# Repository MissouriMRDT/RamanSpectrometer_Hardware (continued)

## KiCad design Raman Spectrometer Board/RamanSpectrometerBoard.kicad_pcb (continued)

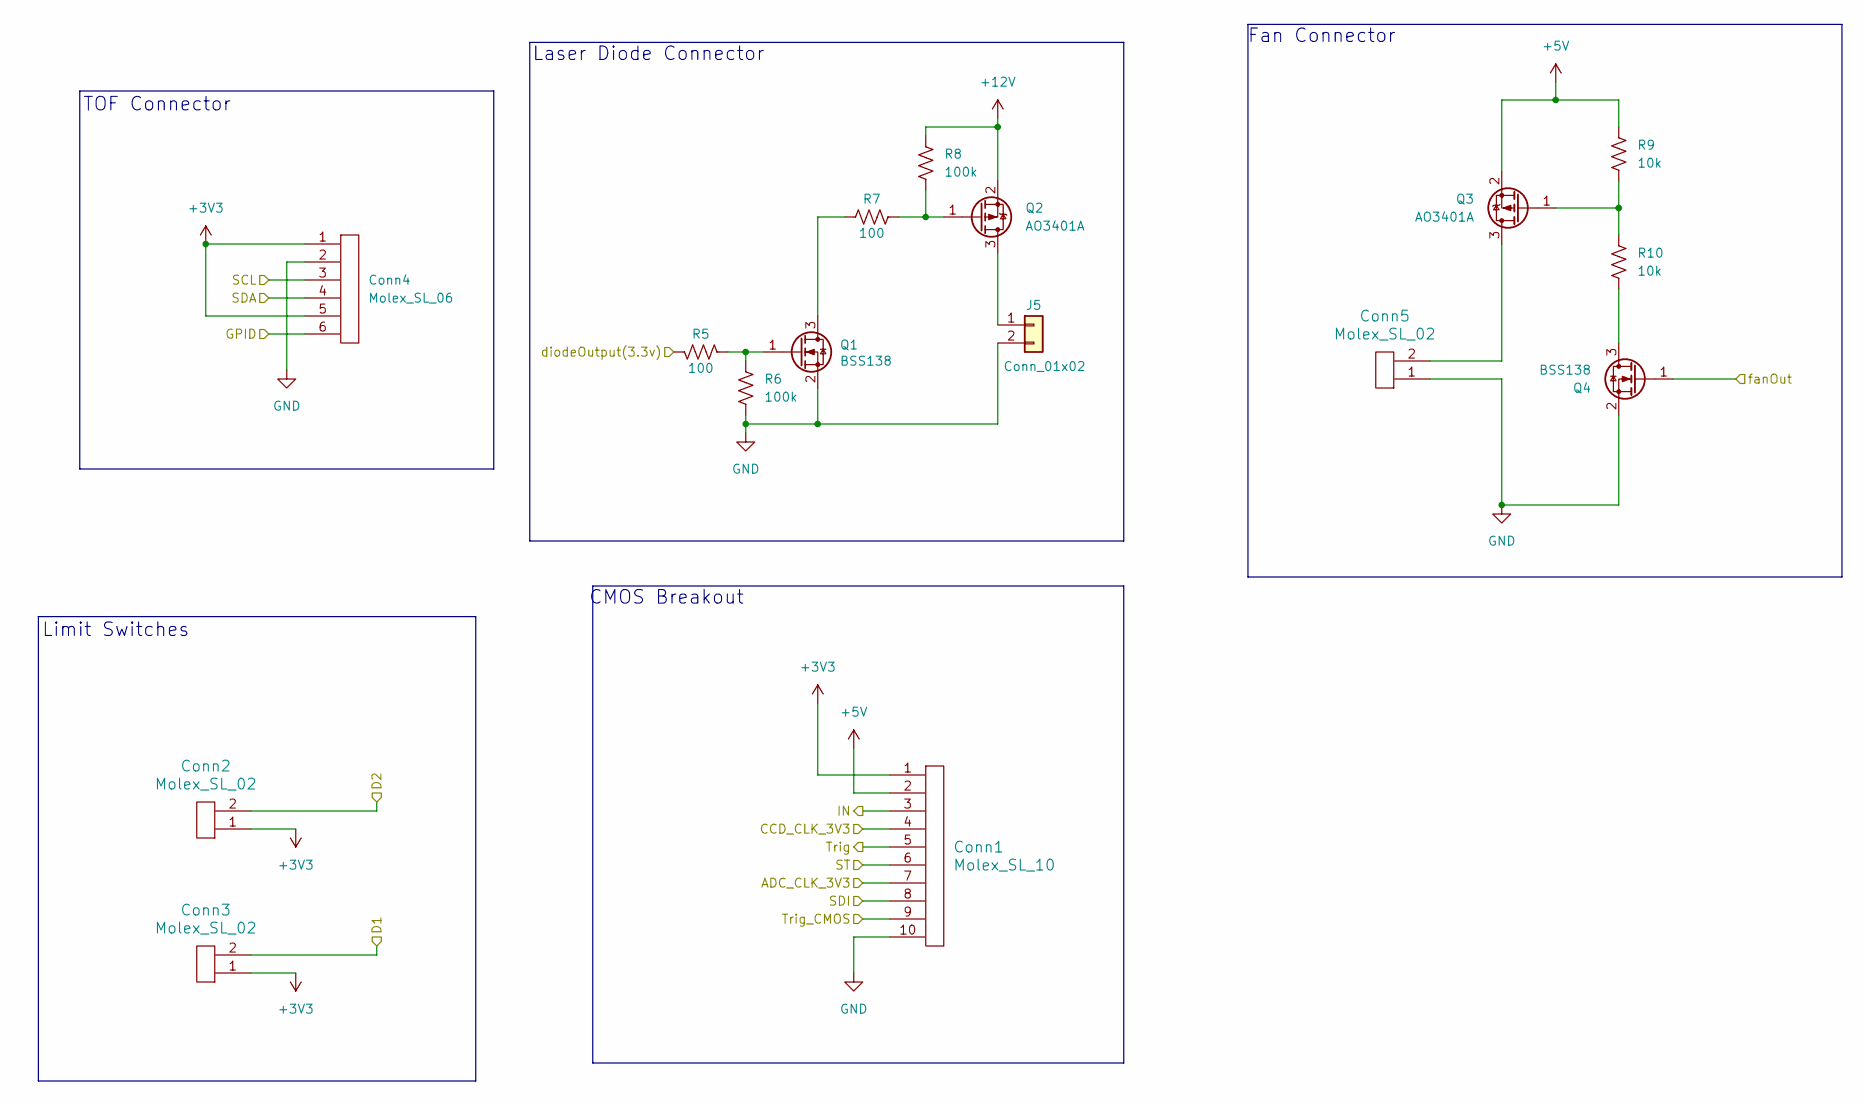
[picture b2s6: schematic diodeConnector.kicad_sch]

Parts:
Conn1: Molex_SL_10; MOLEX_SL_10_Vertical
Conn2, Conn3, Conn5: Molex_SL_02; MOLEX_SL_02_Vertical
Conn4: Molex_SL_06; MOLEX_SL_06_Vertical
J5: Conn_01x02; JST_EH_S2B-EH_1x02_P2.50mm_Horizontal
Q1, Q4: BSS138; SOT-23
Q2, Q3: AO3401A; SOT-23
R5, R7: 100; R_0603_1608Metric_Pad0.98x0.95mm_HandSolder
R6, R8: 100k; R_0603_1608Metric_Pad0.98x0.95mm_HandSolder
R9, R10: 10k; R_0603_1608Metric_Pad0.98x0.95mm_HandSolder

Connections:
+3V3: Conn1.1, Conn2.1, Conn3.1, Conn4.1, Conn4.5; also elsewhere on the board
+5V: Conn1.2, Q3.2 (S), R9.1; also elsewhere on the board
+12V: Q2.2 (S), R8.2; also elsewhere on the board
/Connectors/ADC_CLK_3V3: Conn1.7; also elsewhere on the board
/Connectors/CCD_CLK_3V3: Conn1.4; also elsewhere on the board
/Connectors/D1: Conn3.2; also elsewhere on the board
/Connectors/D2: Conn2.2; also elsewhere on the board
/Connectors/GPID: Conn4.6; also elsewhere on the board
/Connectors/IN: Conn1.3; also elsewhere on the board
/Connectors/SCL: Conn4.3; also elsewhere on the board
/Connectors/SDA: Conn4.4; also elsewhere on the board
/Connectors/SDI: Conn1.8; also elsewhere on the board
/Connectors/ST: Conn1.6; also elsewhere on the board
/Connectors/Trig: Conn1.5; also elsewhere on the board
/Connectors/Trig_CMOS: Conn1.9; also elsewhere on the board
/Connectors/diodeOutput(3.3v): R5.2; also elsewhere on the board
/Connectors/fanOut: Q4.1 (G); also elsewhere on the board
GND: Conn1.10, Conn4.2, Conn5.1, J5.2, Q1.2 (S), Q4.2 (S), R6.1; also elsewhere on the board
unnamed: J5.1, Q2.3 (D)
unnamed: Q1.3 (D), R7.1
unnamed: Q1.1 (G), R5.1, R6.2
unnamed: Q2.1 (G), R7.2, R8.1
unnamed: Conn5.2, Q3.3 (D)
unnamed: Q3.1 (G), R9.2, R10.1
unnamed: Q4.3 (D), R10.2

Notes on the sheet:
CMOS Breakout
Laser Diode Connector
TOF Connector
Limit Switches
Fan Connector

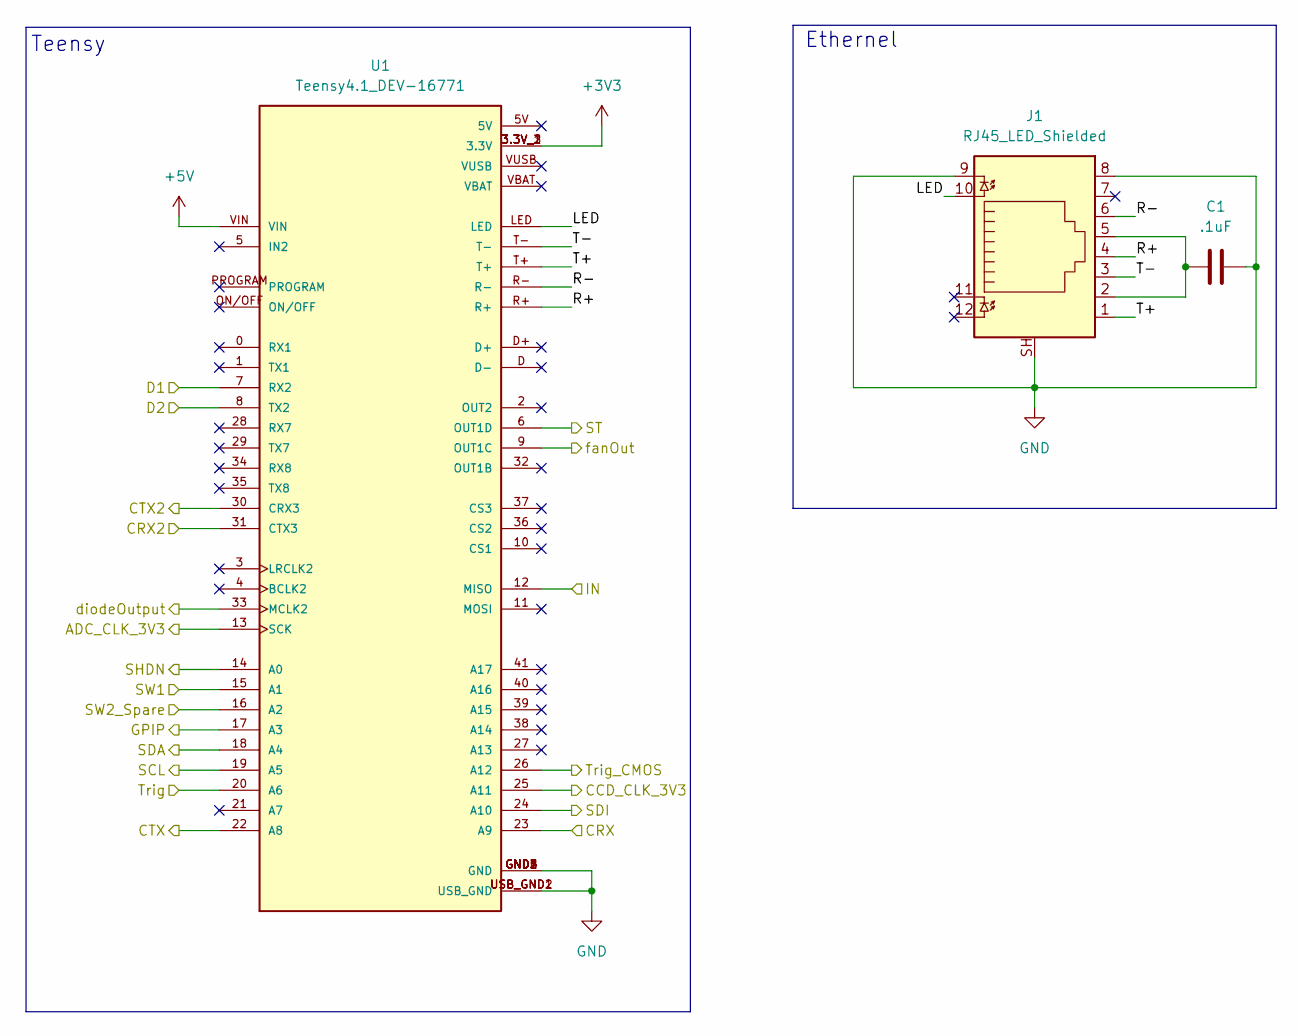
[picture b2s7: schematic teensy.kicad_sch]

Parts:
C1: .1uF; C_0603_1608Metric_Pad1.08x0.95mm_HandSolder
J1: RJ45_LED_Shielded; RJ45_Teensy
U1: Teensy4.1_DEV-16771; Teensy_4_1_Ethernet; PARTREV 4.1

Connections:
+3V3: U1.3.3V_1 (3.3V), U1.3.3V_2 (3.3V), U1.3.3V_3 (3.3V); also elsewhere on the board
+5V: U1.VIN; also elsewhere on the board
/CAN Transceiver/RXD: U1.23 (A9); also elsewhere on the board
/CAN Transceiver/RXD2: U1.31 (CTX3); also elsewhere on the board
/CAN Transceiver/SW1: U1.15 (A1); also elsewhere on the board
/CAN Transceiver/SW2_Spare: U1.16 (A2); also elsewhere on the board
/CAN Transceiver/TXD: U1.22 (A8); also elsewhere on the board
/CAN Transceiver/TXD2: U1.30 (CRX3); also elsewhere on the board
/Connectors/ADC_CLK_3V3: U1.13 (SCK); also elsewhere on the board
/Connectors/CCD_CLK_3V3: U1.25 (A11); also elsewhere on the board
/Connectors/D1: U1.7 (RX2); also elsewhere on the board
/Connectors/D2: U1.8 (TX2); also elsewhere on the board
/Connectors/GPID: U1.17 (A3); also elsewhere on the board
/Connectors/IN: U1.12 (MISO); also elsewhere on the board
/Connectors/SCL: U1.19 (A5); also elsewhere on the board
/Connectors/SDA: U1.18 (A4); also elsewhere on the board
/Connectors/SDI: U1.24 (A10); also elsewhere on the board
/Connectors/ST: U1.6 (OUT1D); also elsewhere on the board
/Connectors/Trig: U1.20 (A6); also elsewhere on the board
/Connectors/Trig_CMOS: U1.26 (A12); also elsewhere on the board
/Connectors/diodeOutput(3.3v): U1.33 (MCLK2); also elsewhere on the board
/Connectors/fanOut: U1.9 (OUT1C); also elsewhere on the board
/LD_Buck/SHDN: U1.14 (A0); also elsewhere on the board
/MCU/LED: J1.10, U1.LED
/MCU/R+: J1.4, U1.R+
/MCU/R-: J1.6, U1.R-
/MCU/T+: J1.1, U1.T+
/MCU/T-: J1.3, U1.T-
GND: C1.2, J1.8, J1.9, J1.SH, U1.GND1 (GND), U1.GND2 (GND), U1.GND3 (GND), U1.GND4 (GND), U1.GND5 (GND), U1.USB_GND1 (USB_GND), U1.USB_GND2 (USB_GND); also elsewhere on the board
unnamed: C1.1, J1.2, J1.5

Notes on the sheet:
Ethernel
Teensy

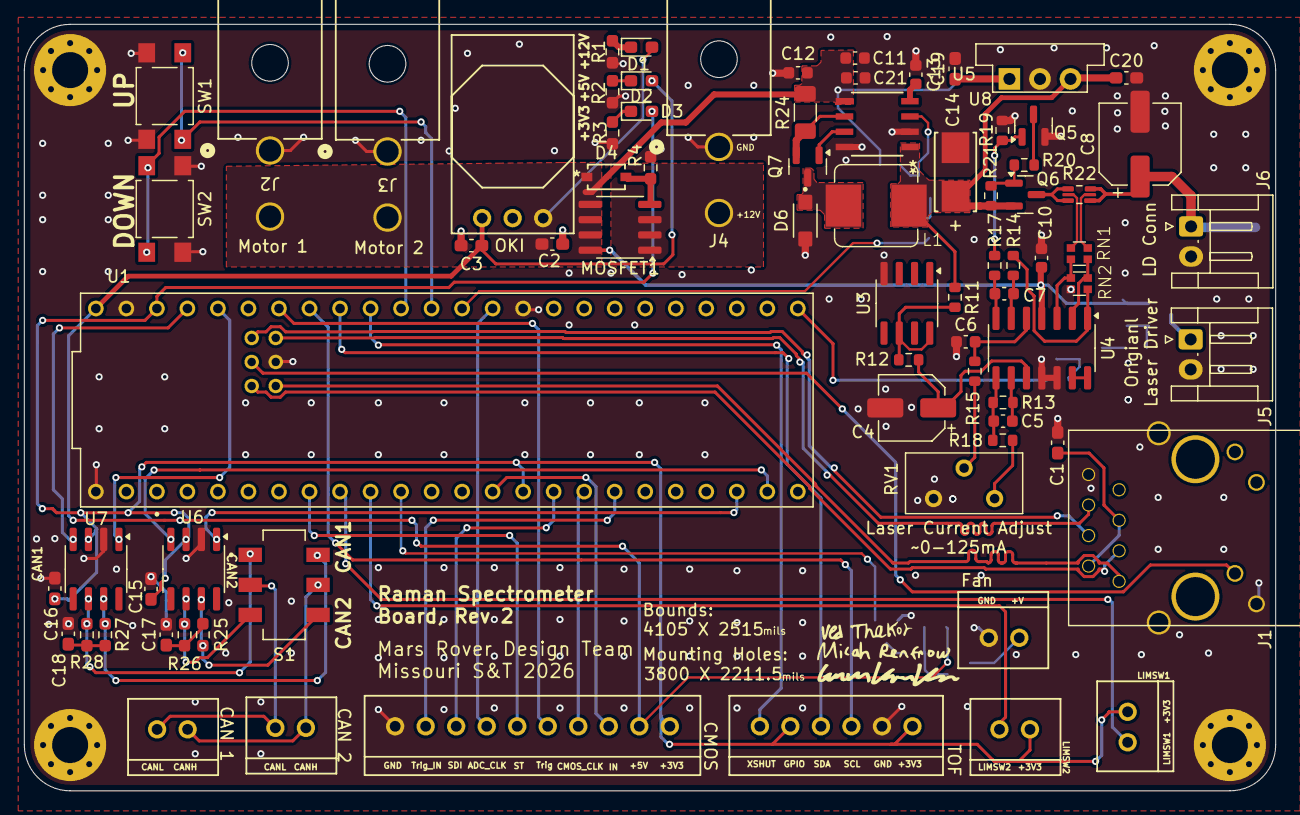
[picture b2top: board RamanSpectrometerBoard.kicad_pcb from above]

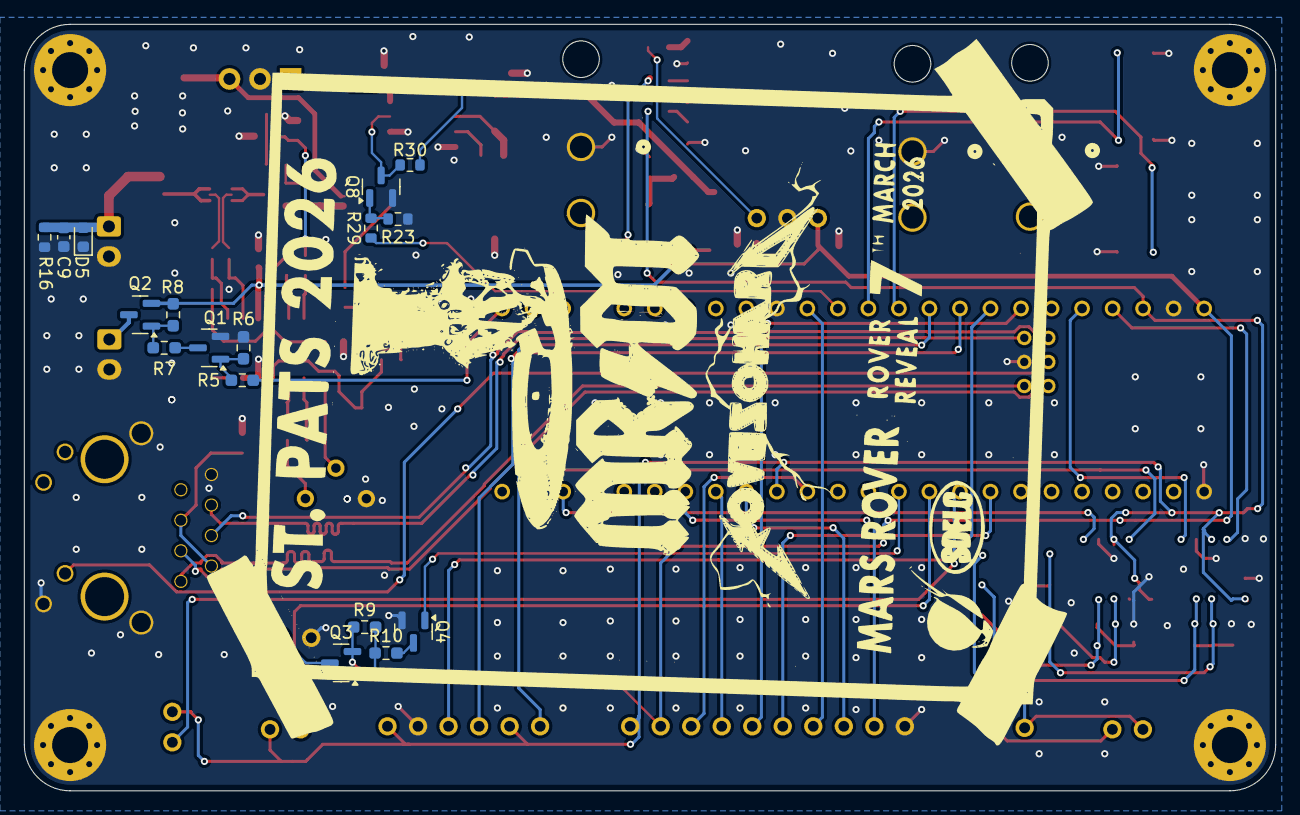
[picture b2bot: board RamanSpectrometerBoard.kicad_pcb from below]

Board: 2 copper layers, 104.1 x 63.8 mm, 98 parts (17 on the bottom side), 78 nets.

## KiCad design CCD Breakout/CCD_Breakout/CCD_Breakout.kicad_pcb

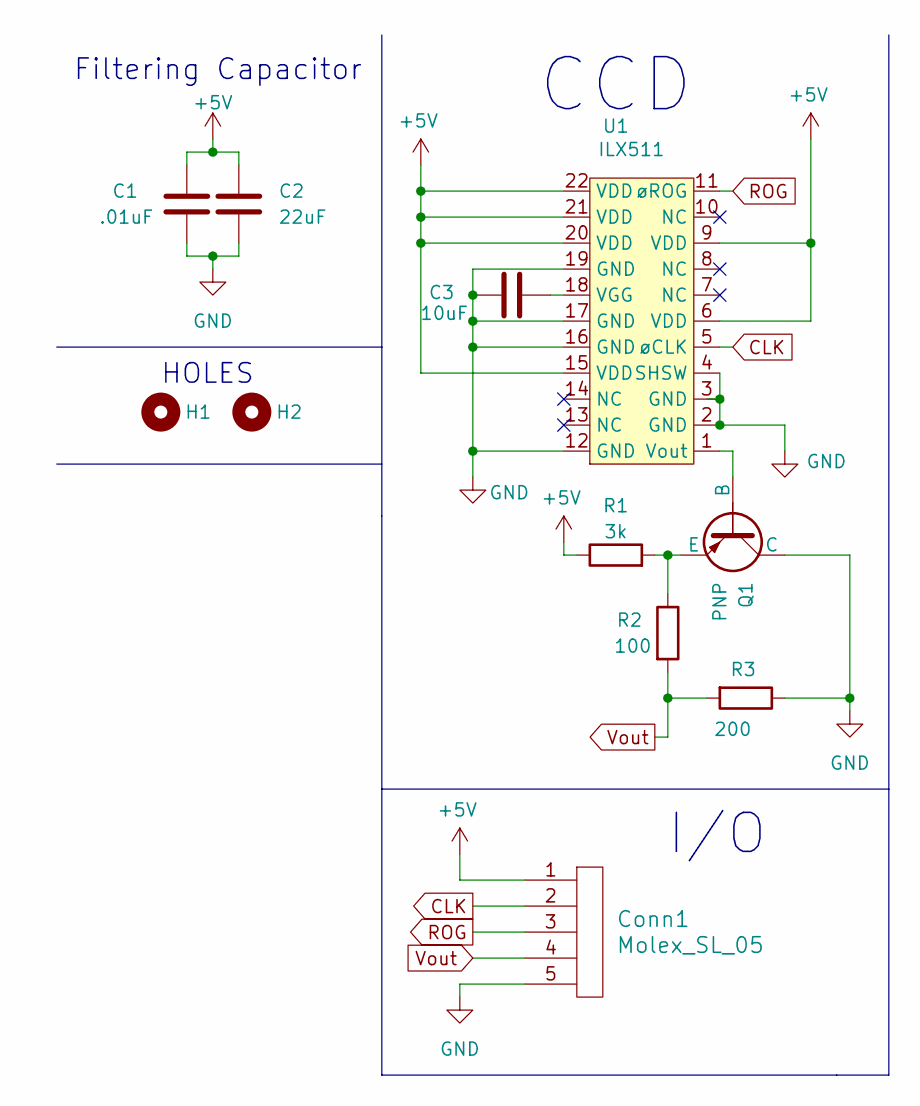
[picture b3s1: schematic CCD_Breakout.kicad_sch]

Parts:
C1: .01uF; C_0603_1608Metric_Pad1.08x0.95mm_HandSolder
C2: 22uF; C_0603_1608Metric_Pad1.08x0.95mm_HandSolder
C3: 10uF; C_0603_1608Metric_Pad1.08x0.95mm_HandSolder
Conn1: Molex_SL_05; MOLEX_SL_05_Vertical
H1, H2: 4_40_Hole
Q1: PNP; SOT-23
R1: 3k; R_0603_1608Metric_Pad0.98x0.95mm_HandSolder
R2: 100; R_0603_1608Metric_Pad0.98x0.95mm_HandSolder
R3: 200; R_0603_1608Metric_Pad0.98x0.95mm_HandSolder
U1: ILX511

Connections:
+5V: C1.1, C2.1, Conn1.1, R1.1, U1.6 (VDD), U1.9 (VDD), U1.15 (VDD), U1.20 (VDD), U1.21 (VDD), U1.22 (VDD)
CLK: Conn1.2, U1.5 (øCLK)
GND: C1.2, C2.2, C3.1, Conn1.5, Q1.3 (C), R3.1, U1.2 (GND), U1.3 (GND), U1.4 (SHSW), U1.12 (GND), U1.16 (GND), U1.17 (GND), U1.19 (GND)
unnamed: Q1.1 (B), U1.1 (Vout)
unnamed: Q1.2 (E), R1.2, R2.1
unnamed: C3.2, U1.18 (VGG)
ROG: Conn1.3, U1.11 (øROG)
Vout: Conn1.4, R2.2, R3.2

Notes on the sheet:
CCD
Filtering Capacitor
HOLES
I/O

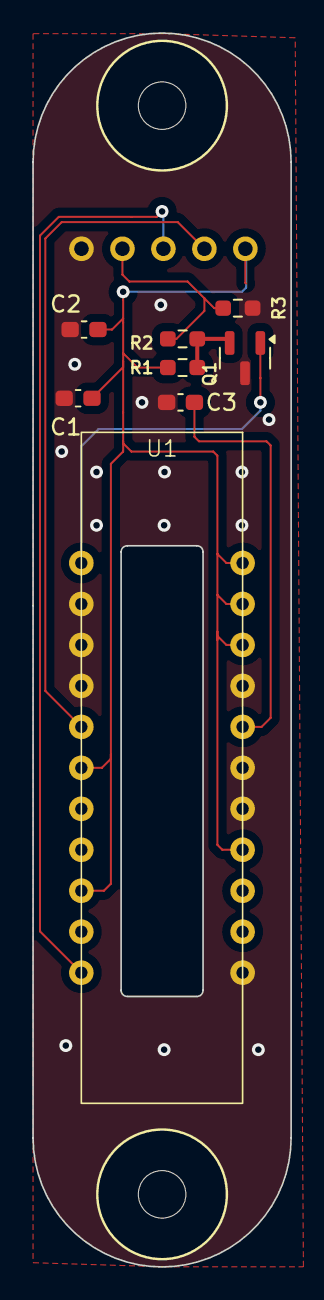
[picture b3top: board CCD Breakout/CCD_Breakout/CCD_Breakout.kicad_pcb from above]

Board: 2 copper layers, 16.0 x 76.5 mm, 11 parts (1 on the bottom side), 8 nets.

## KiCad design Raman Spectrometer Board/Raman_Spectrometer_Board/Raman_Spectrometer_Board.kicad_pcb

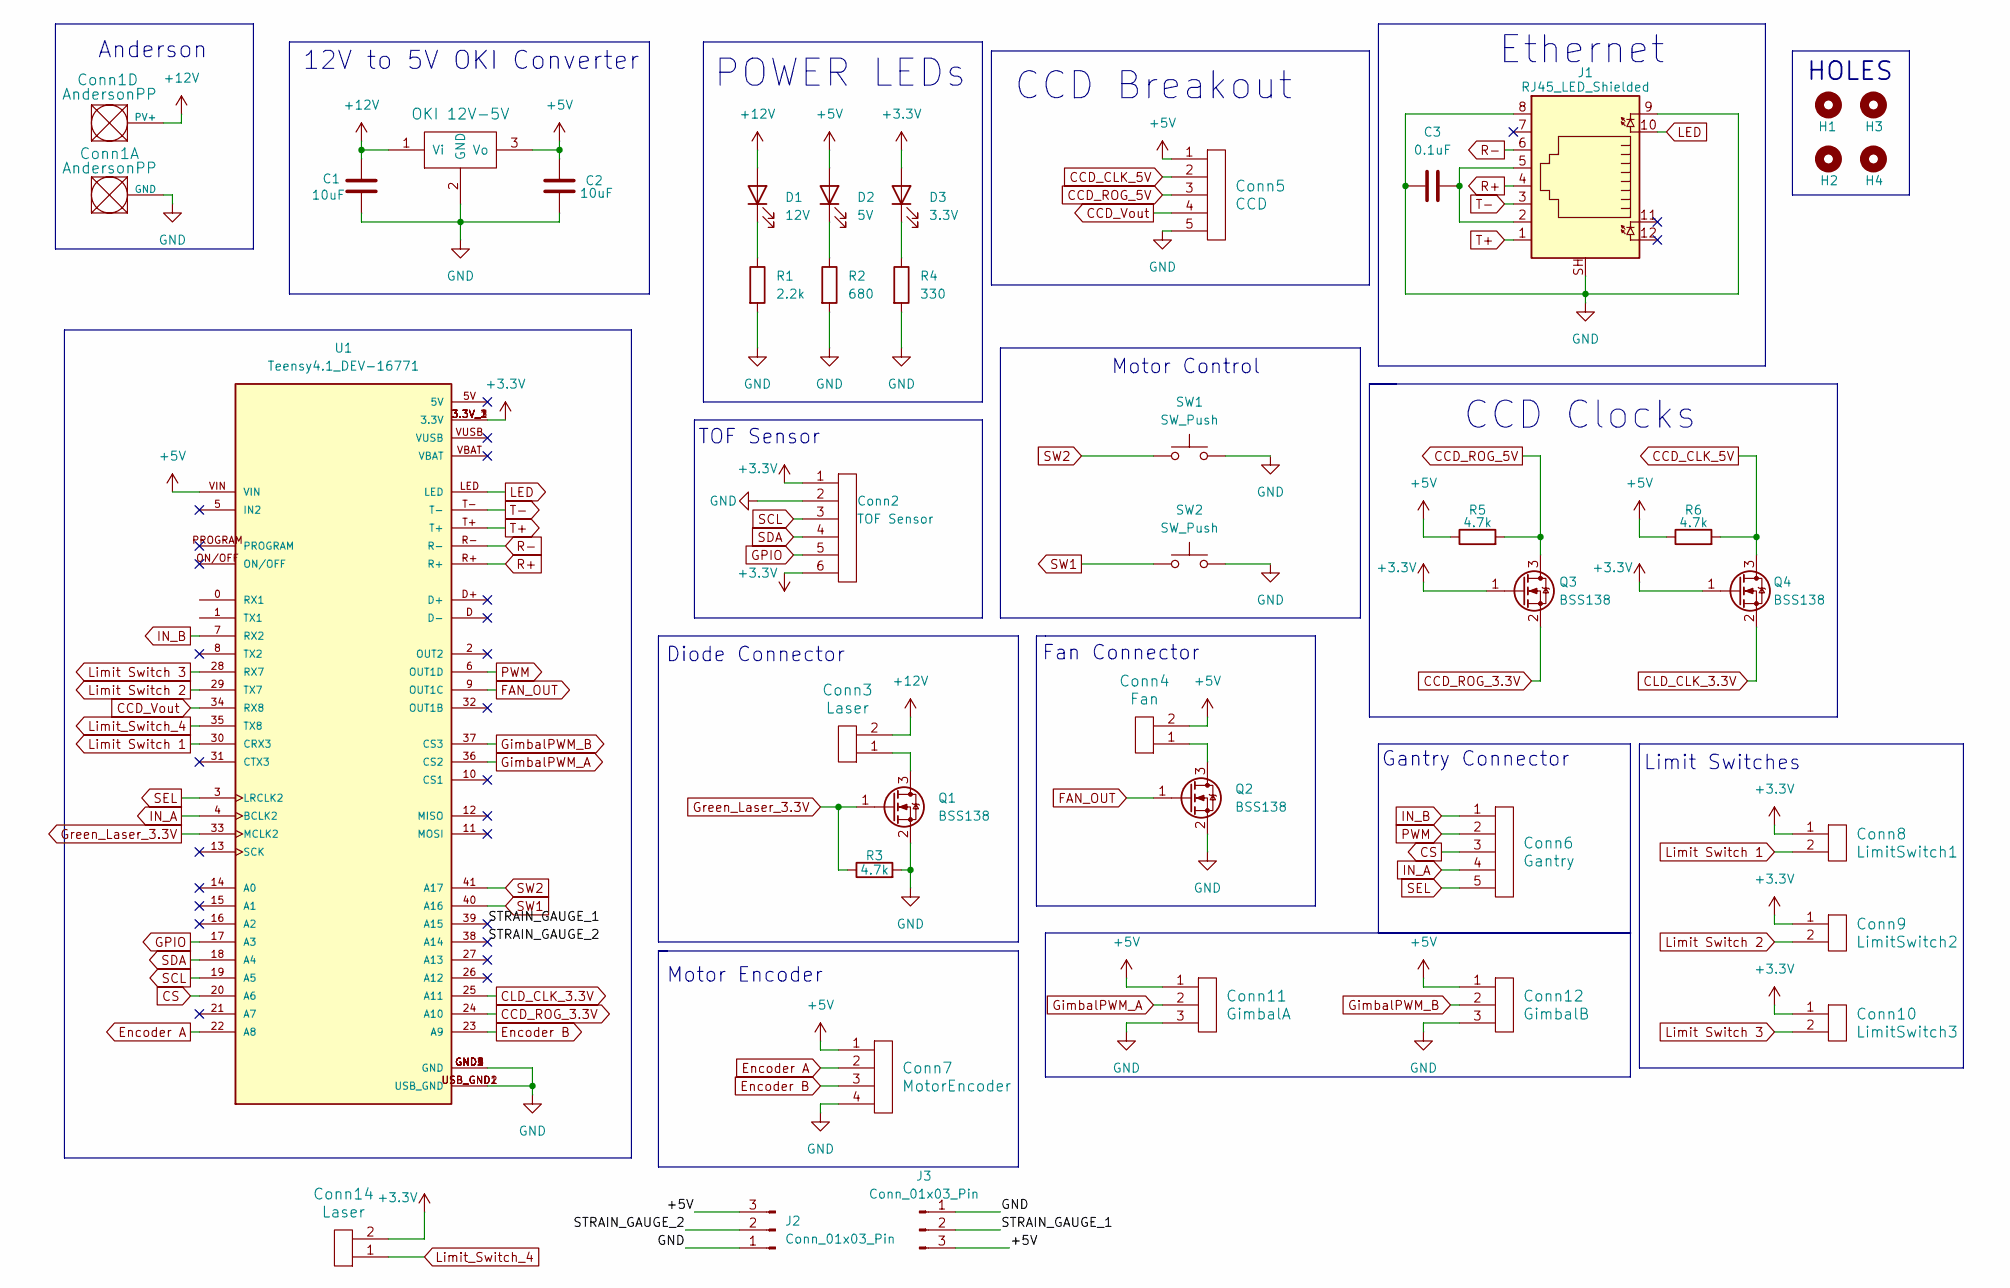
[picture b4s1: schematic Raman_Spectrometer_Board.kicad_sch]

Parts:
C1, C2: 10uF; C_0603_1608Metric_Pad1.08x0.95mm_HandSolder
C3: 0.1uF; C_0603_1608Metric_Pad1.08x0.95mm_HandSolder
Conn1: AndersonPP; Square_Anderson_2_H_Side_By_Side_PV
Conn2: TOF Sensor; MOLEX_SL_06_Vertical
Conn3, Conn14: Laser; MOLEX_SL_02_Vertical
Conn4: Fan; MOLEX_SL_02_Vertical
Conn5: CCD; MOLEX_SL_05_Vertical
Conn6: Gantry; MOLEX_SL_05_Vertical
Conn7: MotorEncoder; MOLEX_SL_04_Vertical
Conn8: LimitSwitch1; MOLEX_SL_02_Vertical
Conn9: LimitSwitch2; MOLEX_SL_02_Vertical
Conn10: LimitSwitch3; MOLEX_SL_02_Vertical
Conn11: GimbalA; MOLEX_SL_03_Vertical
Conn12: GimbalB; MOLEX_SL_03_Vertical
D1: 12V; LED_0603_1608Metric_Pad1.05x0.95mm_HandSolder
D2: 5V; LED_0603_1608Metric_Pad1.05x0.95mm_HandSolder
D3: 3.3V; LED_0603_1608Metric_Pad1.05x0.95mm_HandSolder
H1, H2, H3, H4: 4_40_Hole
J1: RJ45_LED_Shielded; RJ45_Teensy
J2, J3: Conn_01x03_Pin; PinHeader_1x03_P2.54mm_Vertical
Q1, Q2, Q3, Q4: BSS138; SOT-23
R1: 2.2k; R_0603_1608Metric_Pad0.98x0.95mm_HandSolder
R2: 680; R_0603_1608Metric_Pad0.98x0.95mm_HandSolder
R3, R5, R6: 4.7k; R_0603_1608Metric_Pad0.98x0.95mm_HandSolder
R4: 330; R_0603_1608Metric_Pad0.98x0.95mm_HandSolder
SW1, SW2: SW_Push; SW_SPST_TL3305A
U1: Teensy4.1_DEV-16771; Teensy_4_1_Ethernet; PARTREV 4.1
U2: OKI 12V-5V; OKI_Horizontal

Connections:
+3.3V: Conn2.1, Conn2.6, Conn8.1, Conn9.1, Conn10.1, Conn14.2, D3.2 (A), Q3.1 (G), Q4.1 (G), U1.3.3V_1 (3.3V), U1.3.3V_2 (3.3V), U1.3.3V_3 (3.3V)
+5V: C2.1, Conn4.2, Conn5.1, Conn7.1, Conn11.1, Conn12.1, D2.2 (A), J2.3, J3.3, R5.1, R6.1, U1.VIN, U2.3 (Vo)
+12V: C1.1, Conn1.4 (PV+), Conn3.2, D1.2 (A), U2.1 (Vi)
/STRAIN_GAUGE_1: J3.2, U1.39 (A15)
/STRAIN_GAUGE_2: J2.2, U1.38 (A14)
CCD_CLK_5V: Conn5.2, Q4.3 (D), R6.2
CCD_ROG_3.3V: Q3.2 (S), U1.24 (A10)
CCD_ROG_5V: Conn5.3, Q3.3 (D), R5.2
CCD_Vout: Conn5.4, U1.34 (RX8)
CLD_CLK_3.3V: Q4.2 (S), U1.25 (A11)
CS: Conn6.3, U1.20 (A6)
Encoder A: Conn7.2, U1.22 (A8)
Encoder B: Conn7.3, U1.23 (A9)
FAN_OUT: Q2.1 (G), U1.9 (OUT1C)
GND: C1.2, C2.2, C3.2, Conn1.1 (GND), Conn2.2, Conn5.5, Conn7.4, Conn11.3, Conn12.3, J1.8, J1.9, J1.SH, J2.1, J3.1, Q1.2 (S), Q2.2 (S), R1.2, R2.2, R3.2, R4.2, SW1.2, SW2.2, U1.GND1 (GND), U1.GND2 (GND), U1.GND3 (GND), U1.GND4 (GND), U1.GND5 (GND), U1.USB_GND1 (USB_GND), U1.USB_GND2 (USB_GND), U2.2 (GND)
GPIO: Conn2.5, U1.17 (A3)
GimbalPWM_A: Conn11.2, U1.36 (CS2)
GimbalPWM_B: Conn12.2, U1.37 (CS3)
Green_Laser_3.3V: Q1.1 (G), R3.1, U1.33 (MCLK2)
IN_A: Conn6.4, U1.4 (BCLK2)
IN_B: Conn6.1, U1.7 (RX2)
LED: J1.10, U1.LED
Limit Switch 1: Conn8.2, U1.30 (CRX3)
Limit Switch 2: Conn9.2, U1.29 (TX7)
Limit Switch 3: Conn10.2, U1.28 (RX7)
Limit_Switch_4: Conn14.1, U1.35 (TX8)
unnamed: C3.1, J1.2, J1.5
unnamed: D1.1 (K), R1.1
unnamed: D2.1 (K), R2.1
unnamed: D3.1 (K), R4.1
unnamed: Conn3.1, Q1.3 (D)
unnamed: Conn4.1, Q2.3 (D)
PWM: Conn6.2, U1.6 (OUT1D)
R+: J1.4, U1.R+
R-: J1.6, U1.R-
SCL: Conn2.3, U1.19 (A5)
SDA: Conn2.4, U1.18 (A4)
SEL: Conn6.5, U1.3 (LRCLK2)
SW1: SW2.1, U1.40 (A16)
SW2: SW1.1, U1.41 (A17)
T+: J1.1, U1.T+
T-: J1.3, U1.T-

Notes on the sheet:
Gantry Connector
12V to 5V OKI Converter
Ethernet
Fan Connector
Motor Encoder
Diode Connector
HOLES
Motor Control
POWER LEDs
CCD Breakout
CCD Clocks
TOF Sensor
Limit Switches
Anderson

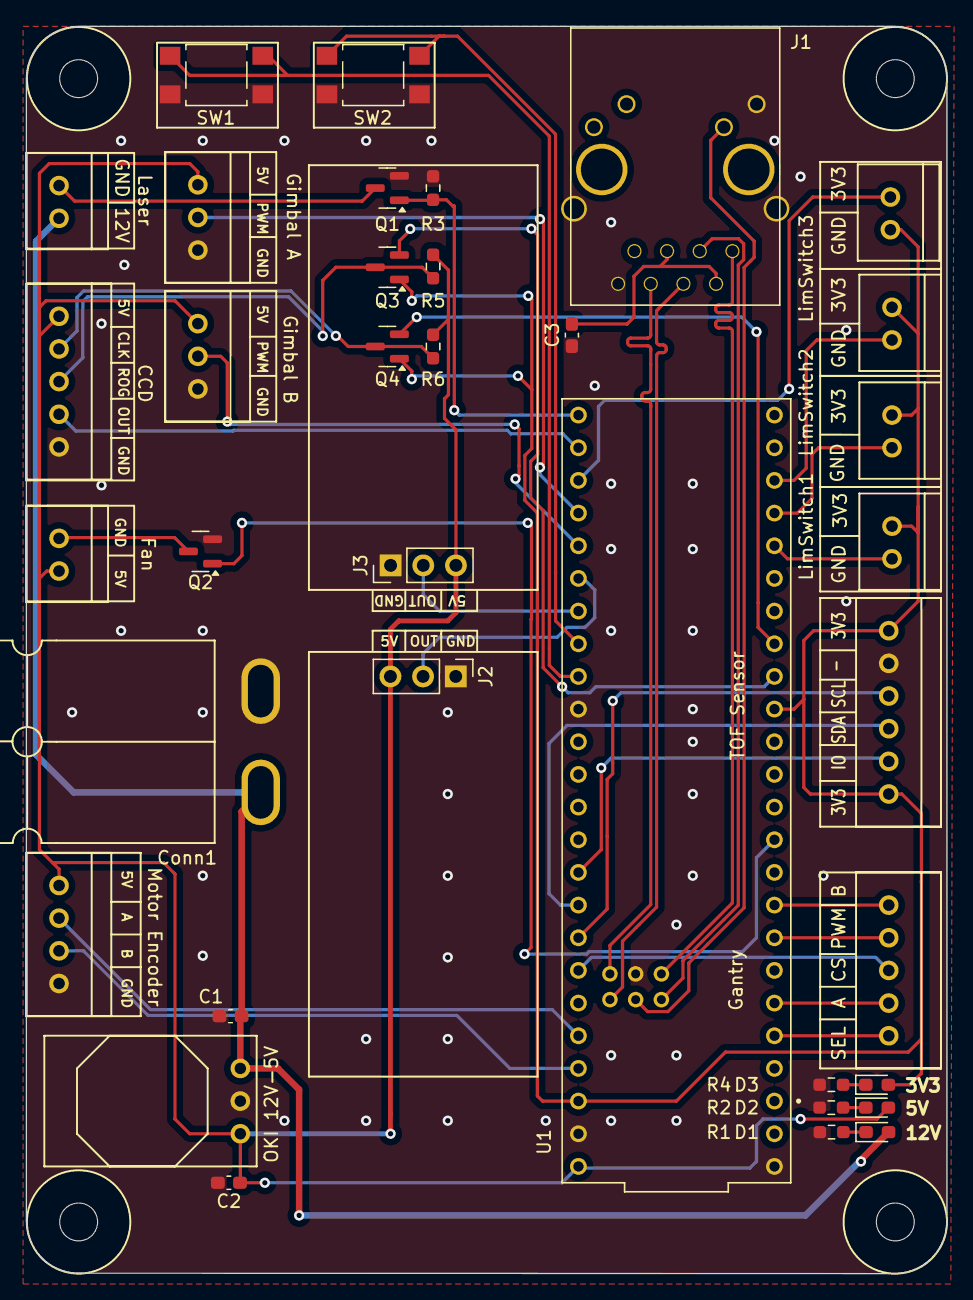
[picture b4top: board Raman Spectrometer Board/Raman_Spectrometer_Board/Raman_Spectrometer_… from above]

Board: 2 copper layers, 71.6 x 97.0 mm, 40 parts (0 on the bottom side), 42 nets.

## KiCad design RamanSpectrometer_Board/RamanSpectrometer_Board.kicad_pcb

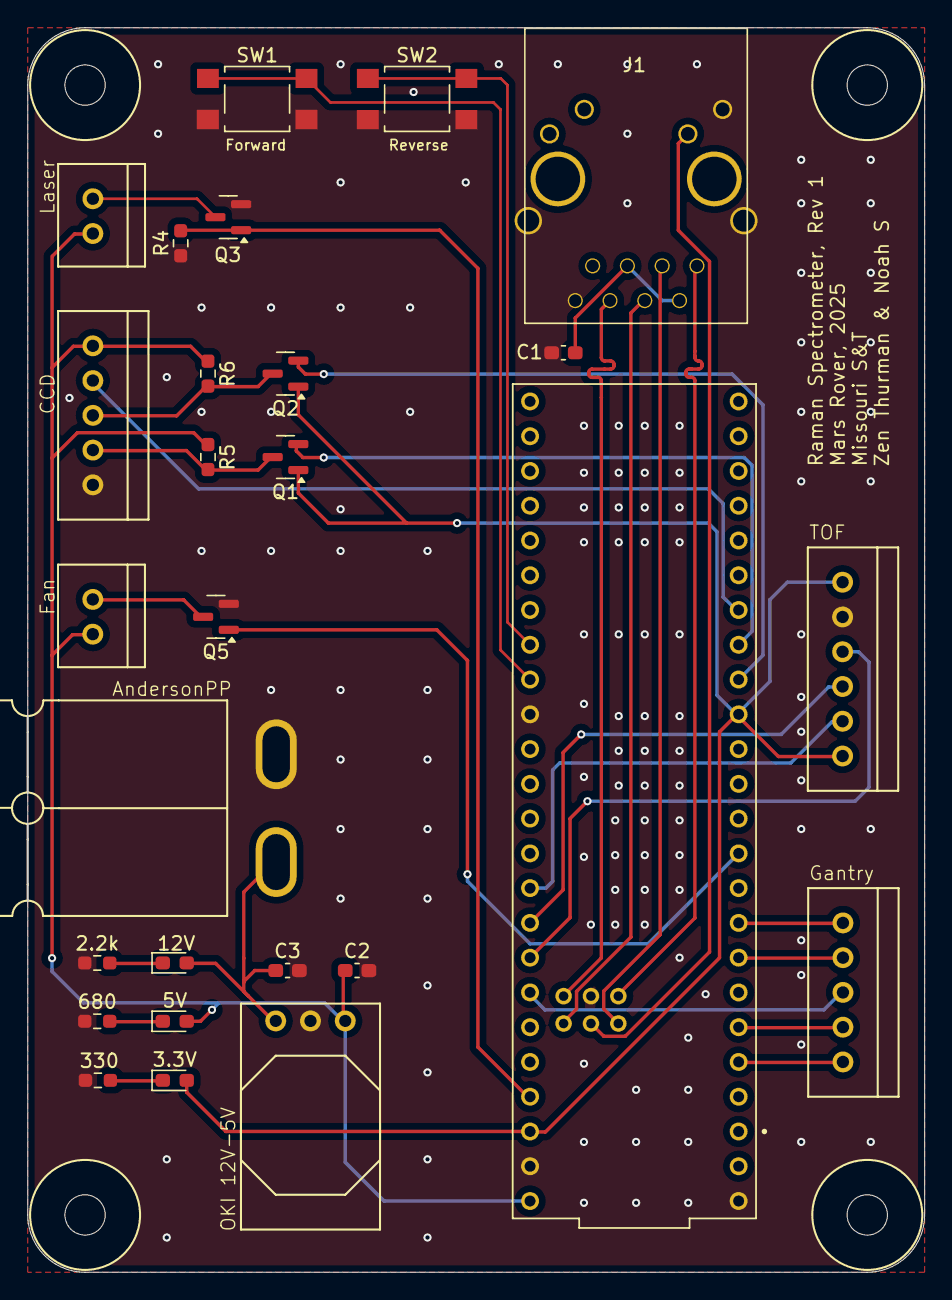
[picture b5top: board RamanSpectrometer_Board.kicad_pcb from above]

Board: 2 copper layers, 65.5 x 90.9 mm, 31 parts (0 on the bottom side), 32 nets.

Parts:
C1: 0.1uF; C_0603_1608Metric_Pad1.08x0.95mm_HandSolder
C2, C3: 10uF; C_0603_1608Metric_Pad1.08x0.95mm_HandSolder
Conn1: AndersonPP; Square_Anderson_2_H_Side_By_Side_PV
Conn2: Gantry; MOLEX_SL_05_Vertical
Conn4: CCD; MOLEX_SL_05_Vertical
Conn5: Fan; MOLEX_SL_02_Vertical
Conn6: Laser; MOLEX_SL_02_Vertical
Conn7: TOF Sensor; MOLEX_SL_06_Vertical
D1: 12V; LED_0603_1608Metric_Pad1.05x0.95mm_HandSolder
D2: 5V; LED_0603_1608Metric_Pad1.05x0.95mm_HandSolder
D3: 3.3V; LED_0603_1608Metric_Pad1.05x0.95mm_HandSolder
H1, H2, H3, H4: 4_40_Hole
J1: RJ45_LED_Shielded; RJ45_Teensy
Q1, Q2, Q3, Q5: BSS138; SOT-23
R1: 2.2k; R_0603_1608Metric_Pad0.98x0.95mm_HandSolder
R2: 680; R_0603_1608Metric_Pad0.98x0.95mm_HandSolder
R3: 330; R_0603_1608Metric_Pad0.98x0.95mm_HandSolder
R4, R5, R6: 4.7k; R_0603_1608Metric_Pad0.98x0.95mm_HandSolder
SW1, SW2: SW_Push; SW_SPST_TL3305A
U1: Teensy4.1_DEV-16771; Teensy_4_1_Ethernet
U2: OKI 12V-5V; OKI_Horizontal

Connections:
+3.3V: Conn7.1, Conn7.6, D3.2 (A), Q1.1 (G), Q2.1 (G), U1.3.3V_1 (3.3V), U1.3.3V_2 (3.3V)
+5V: C2.1, Conn4.1, Conn5.2, Conn6.2, D2.2 (A), R5.1, R6.1, U1.VIN, U2.3 (Vo)
+12V: C3.1, Conn1.4 (PV+), D1.2 (A), U2.1 (Vi)
CCD_CLK_5V: Conn4.4, Q1.3 (D), R5.2
CCD_ROG_3.3V: Q2.2 (S), U1.24 (A10)
CCD_ROG_5V: Conn4.3, Q2.3 (D), R6.2
CCD_Vout: Conn4.2, U1.26 (A12)
CLD_CLK_3.3V: Q1.2 (S), U1.25 (A11)
CS: Conn2.3, U1.20 (A6)
FAN_OUT: Q5.1 (G), U1.9 (OUT1C)
GND: C1.2, C2.2, C3.2, Conn1.1 (GND), Conn4.5, Conn7.2, J1.8, J1.9, J1.SH, Q3.2 (S), Q5.2 (S), R1.2, R2.2, R3.2, R4.2, SW1.2, SW2.2, U1.GND1 (GND), U1.GND2 (GND), U1.GND3 (GND), U1.GND5 (GND), U2.2 (GND)
GPIO: Conn7.5, U1.17 (A3)
Green_Laser_3.3V: Q3.1 (G), R4.1, U1.23 (A9)
IN_A: Conn2.4, U1.4 (BCLK2)
IN_B: Conn2.1, U1.7 (RX2)
LED: J1.10, U1.LED
unnamed: C1.1, J1.2, J1.5
unnamed: D1.1 (K), R1.1
unnamed: D2.1 (K), R2.1
unnamed: D3.1 (K), R3.1
unnamed: Conn6.1, Q3.3 (D)
unnamed: Conn5.1, Q5.3 (D)
PWM: Conn2.2, U1.6 (OUT1D)
R+: J1.4, U1.R+
R-: J1.6, U1.R-
SCL: Conn7.3, U1.19 (A5)
SDA: Conn7.4, U1.18 (A4)
SEL: Conn2.5, U1.3 (LRCLK2)
SW1: SW1.1, U1.41 (A17)
SW2: SW2.1, U1.40 (A16)
T+: J1.1, U1.T+
T-: J1.3, U1.T-

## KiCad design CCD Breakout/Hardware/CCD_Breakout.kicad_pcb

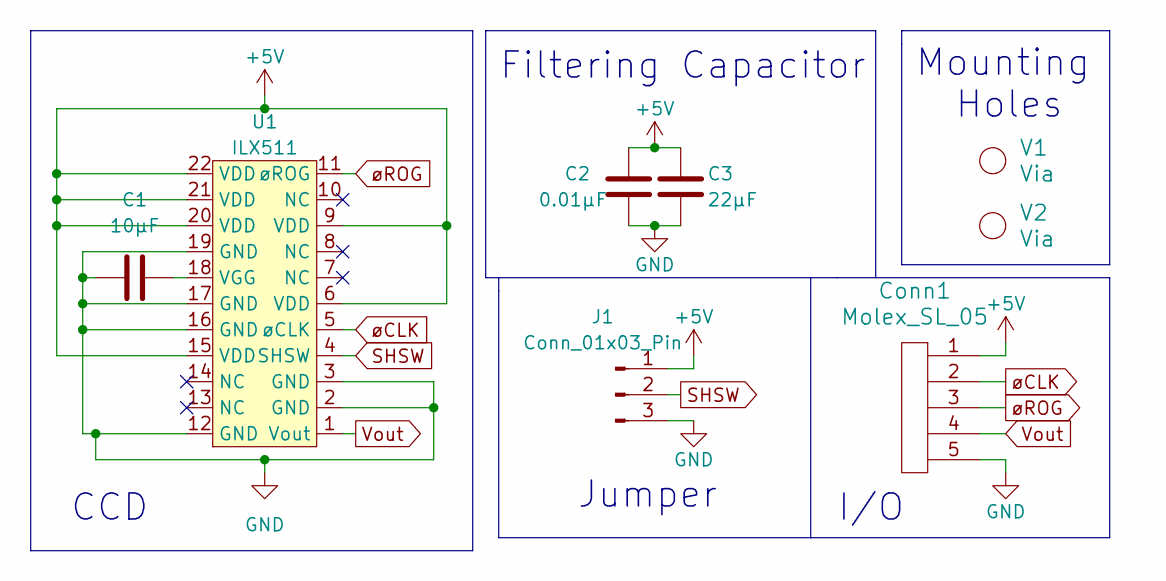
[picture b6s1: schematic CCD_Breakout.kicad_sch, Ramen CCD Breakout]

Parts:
C1: 10µF; C_0603_1608Metric_Pad1.08x0.95mm_HandSolder
C2: 0.01µF; C_0603_1608Metric_Pad1.08x0.95mm_HandSolder
C3: 22µF; C_0603_1608Metric_Pad1.08x0.95mm_HandSolder
Conn1: Molex_SL_05; MOLEX_SL_05_Vertical
J1: Conn_01x03_Pin; PinHeader_1x03_P2.54mm_Vertical
U1: ILX511
V1, V2: Via; 4_40_Hole

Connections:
+5V: C2.2, C3.2, Conn1.1, J1.1, U1.6 (VDD), U1.9 (VDD), U1.15 (VDD), U1.20 (VDD), U1.21 (VDD), U1.22 (VDD)
GND: C1.1, C2.1, C3.1, Conn1.5, J1.3, U1.2 (GND), U1.3 (GND), U1.12 (GND), U1.16 (GND), U1.17 (GND), U1.19 (GND)
unnamed: C1.2, U1.18 (VGG)
SHSW: J1.2, U1.4 (SHSW)
Vout: Conn1.4, U1.1 (Vout)
øCLK: Conn1.2, U1.5 (øCLK)
øROG: Conn1.3, U1.11 (øROG)

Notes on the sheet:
Filtering Capacitor
I/O
CCD
Mounting Holes
Jumper

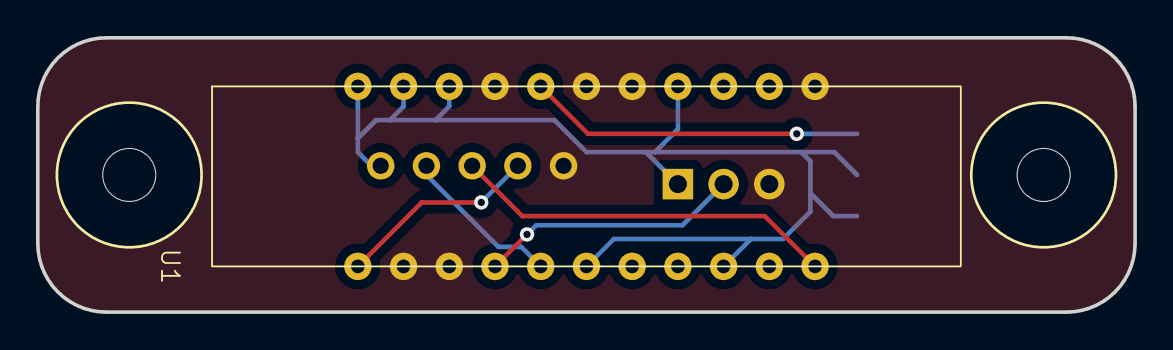
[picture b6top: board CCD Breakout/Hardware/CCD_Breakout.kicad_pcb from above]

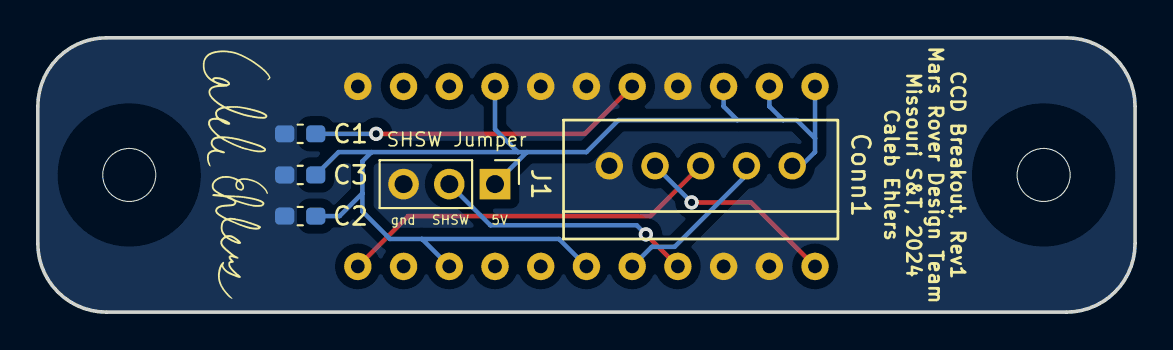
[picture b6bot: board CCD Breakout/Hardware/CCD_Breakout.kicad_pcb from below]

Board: 2 copper layers, 61.0 x 15.2 mm, 8 parts (5 on the bottom side), 7 nets.

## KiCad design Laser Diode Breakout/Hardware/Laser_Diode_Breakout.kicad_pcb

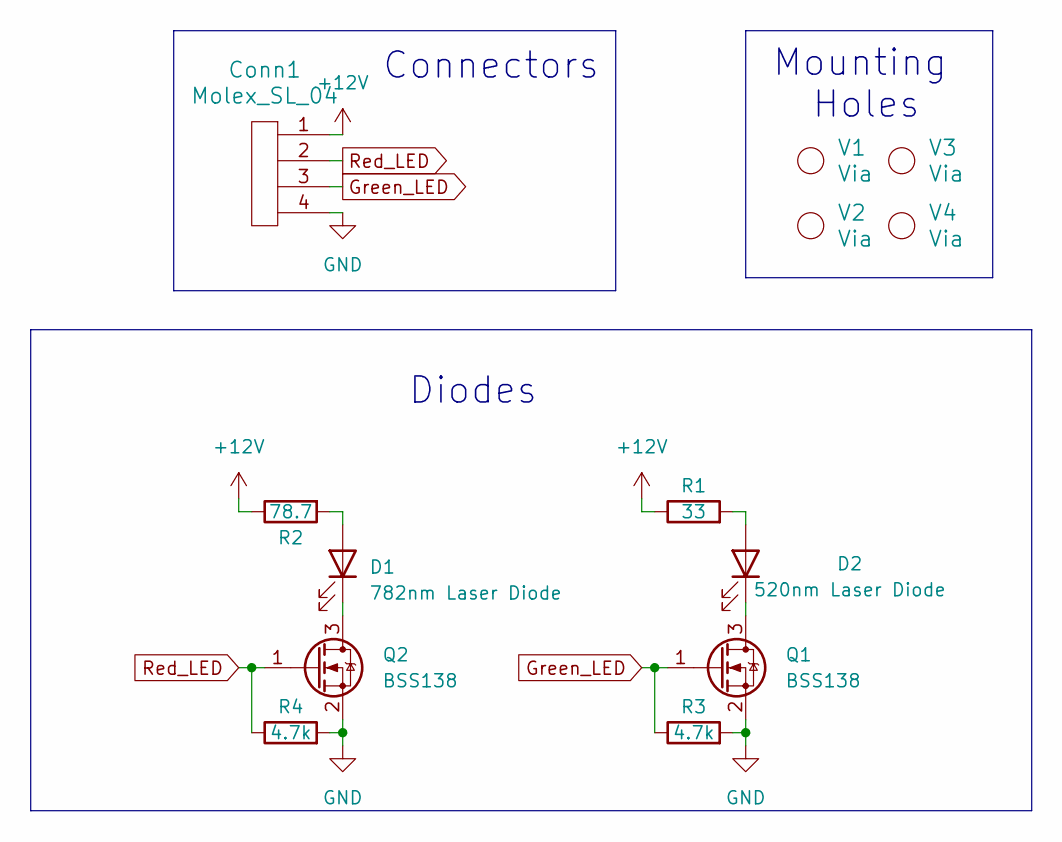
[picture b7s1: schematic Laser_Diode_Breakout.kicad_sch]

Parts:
Conn1: Molex_SL_04; MOLEX_SL_04_Vertical
D1: 782nm Laser Diode; TO-18-3
D2: 520nm Laser Diode; PLT5520B - 520nm
Q1, Q2: BSS138; SOT-23
R1: 33; R_2512_6332Metric_Pad1.40x3.35mm_HandSolder
R2: 78.7; R_1206_3216Metric_Pad1.30x1.75mm_HandSolder
R3, R4: 4.7k; R_0603_1608Metric_Pad0.98x0.95mm_HandSolder
V1, V2, V3, V4: Via; 4_40_Hole

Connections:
+12V: Conn1.1, R1.1, R2.1
GND: Conn1.4, Q1.2 (S), Q2.2 (S), R3.2, R4.2
Green_LED: Conn1.3, Q1.1 (G), R3.1
unnamed: D1.2 (A), R2.2
unnamed: D1.1 (K), Q2.3 (D)
unnamed: D2.2 (A), R1.2
unnamed: D2.1 (K), Q1.3 (D)
Red_LED: Conn1.2, Q2.1 (G), R4.1

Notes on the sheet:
Mounting Holes
Connectors
Diodes
